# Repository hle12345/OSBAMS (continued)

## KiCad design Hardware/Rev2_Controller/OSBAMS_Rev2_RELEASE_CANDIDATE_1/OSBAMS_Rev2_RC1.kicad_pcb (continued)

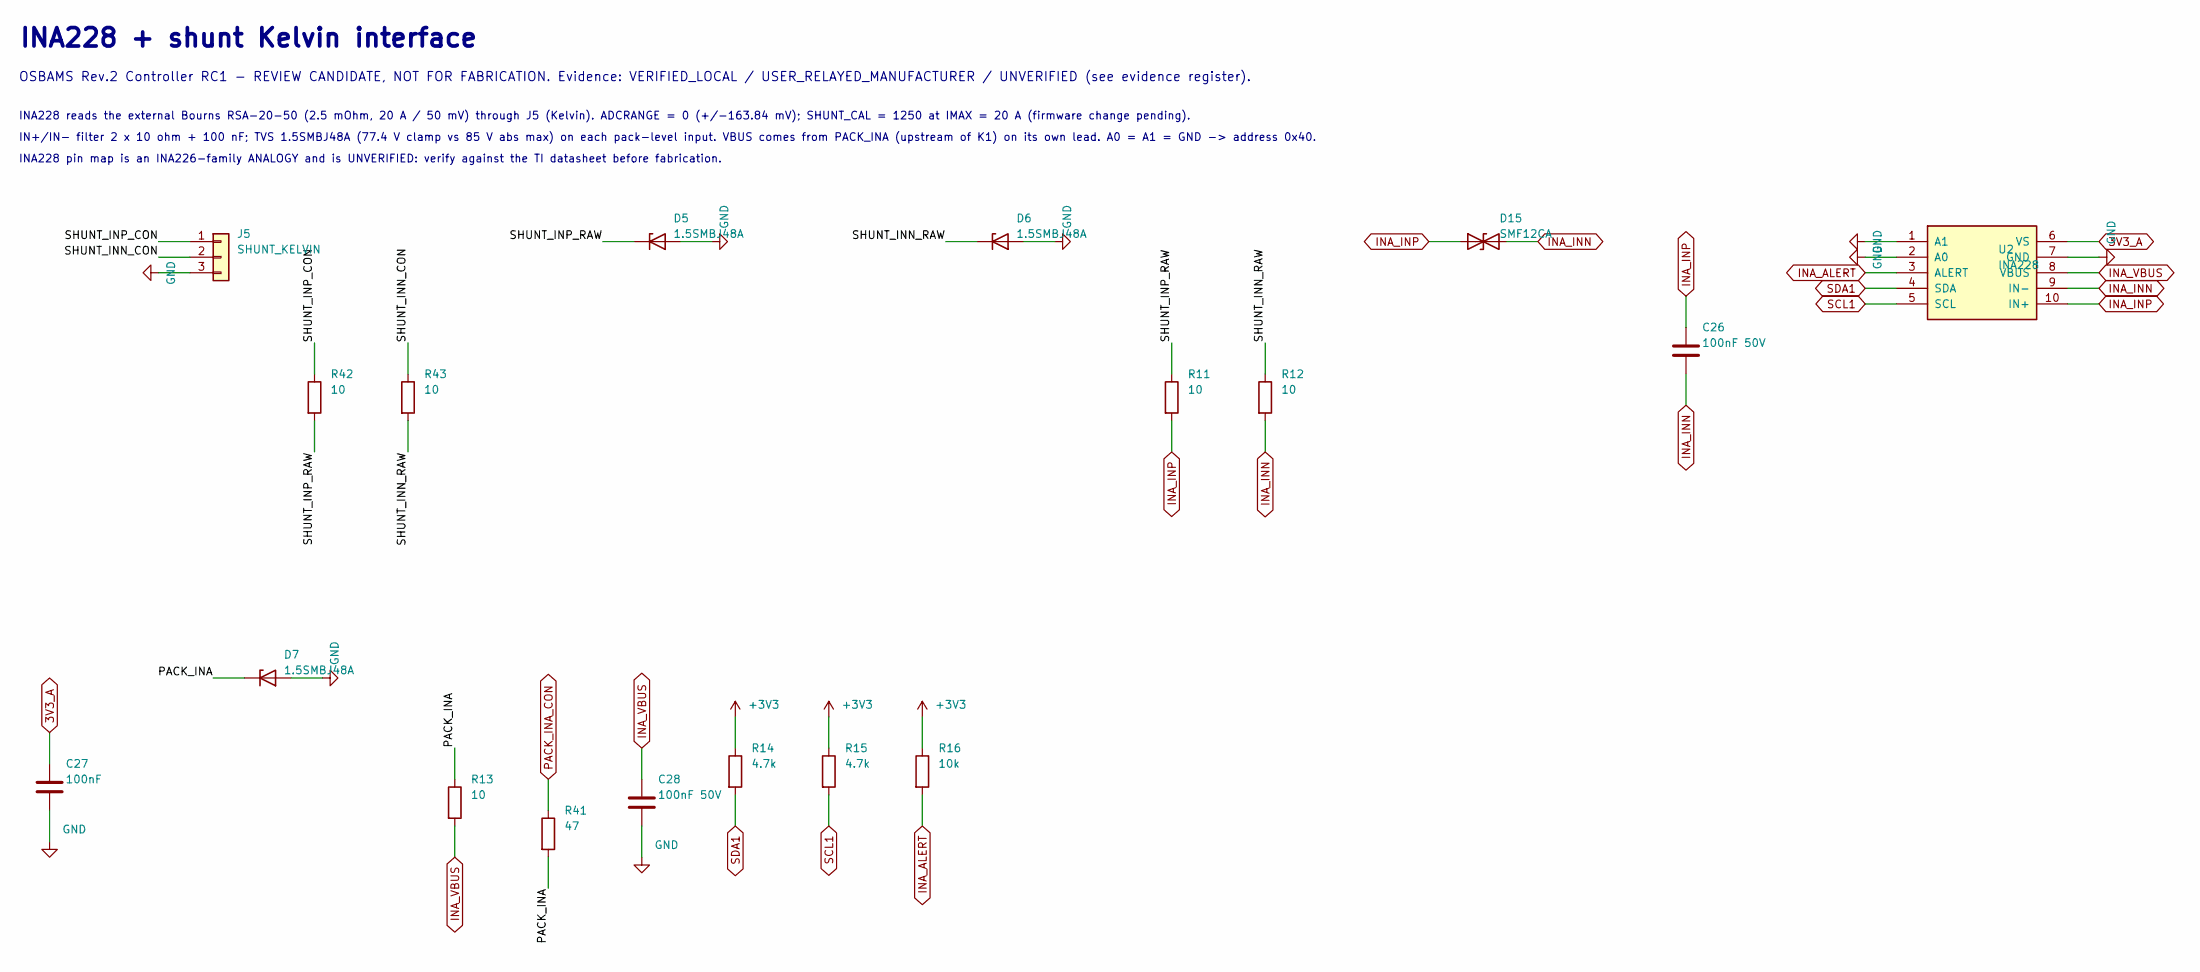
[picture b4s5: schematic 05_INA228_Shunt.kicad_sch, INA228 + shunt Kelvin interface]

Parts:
C26, C28: 100nF 50V; C_0603_1608Metric; MPN GRM188R71H104KA93D
C27: 100nF; C_0603_1608Metric; MPN GRM188R71H104KA93D
D5, D6, D7: 1.5SMBJ48A; D_SMB; MPN 1.5SMBJ48A
D15: SMF12CA; D_SMF; MPN SMF12CA
J5: SHUNT_KELVIN; Molex_KK-254_AE-6410-03A_1x03_P2.54mm_Vertical; MPN 22-27-2031
R11, R12, R13: 10; R_0603_1608Metric; MPN CRCW060310R0FKEA
R14, R15: 4.7k; R_0603_1608Metric; MPN CRCW06034K70FKEA
R16: 10k; R_0603_1608Metric; MPN CRCW060310K0FKEA
R41: 47; R_1206_3216Metric; MPN ERJ-P08F47R0V
R42, R43: 10; R_1206_3216Metric; MPN ERJ-P08F10R0V
U2: INA228; MSOP-10_3x3mm_P0.5mm; MPN INA228AIDGSR

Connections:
3V3_A: C27.1, U2.6 (VS); also elsewhere on the board
+3V3: R14.1, R15.1, R16.1; also elsewhere on the board
/05_INA228_Shunt/PACK_INA: D7.1 (K), R13.1, R41.2
/05_INA228_Shunt/SHUNT_INN_CON: J5.2, R43.1
/05_INA228_Shunt/SHUNT_INN_RAW: D6.1 (K), R12.1, R43.2
/05_INA228_Shunt/SHUNT_INP_CON: J5.1, R42.1
/05_INA228_Shunt/SHUNT_INP_RAW: D5.1 (K), R11.1, R42.2
GND: C27.2, C28.2, D5.2 (A), D6.2 (A), D7.2 (A), J5.3, U2.1 (A1), U2.2 (A0), U2.7 (GND); also elsewhere on the board
INA_ALERT: R16.2, U2.3 (ALERT); also elsewhere on the board
INA_INN: C26.2, D15.2 (A2), R12.2, U2.9 (IN-); also elsewhere on the board
INA_INP: C26.1, D15.1 (A1), R11.2, U2.10 (IN+); also elsewhere on the board
INA_VBUS: C28.1, R13.2, U2.8 (VBUS); also elsewhere on the board
PACK_INA_CON: R41.1; also elsewhere on the board
SCL1: R15.2, U2.5 (SCL); also elsewhere on the board
SDA1: R14.2, U2.4 (SDA); also elsewhere on the board

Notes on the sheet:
INA228 pin map is an INA226-family ANALOGY and is UNVERIFIED: verify against the TI datasheet before fabrication.
IN+/IN- filter 2 x 10 ohm + 100 nF; TVS 1.5SMBJ48A (77.4 V clamp vs 85 V abs max) on each pack-level input. VBUS comes from PACK_INA (upstream of K1) on its own lead. A0 = A1 = GND -> address 0x40.
OSBAMS Rev.2 Controller RC1 - REVIEW CANDIDATE, NOT FOR FABRICATION. Evidence: VERIFIED_LOCAL / USER_RELAYED_MANUFACTURER / UNVERIFIED (see evidence register).
INA228 + shunt Kelvin interface
INA228 reads the external Bourns RSA-20-50 (2.5 mOhm, 20 A / 50 mV) through J5 (Kelvin). ADCRANGE = 0 (+/-163.84 mV); SHUNT_CAL = 1250 at IMAX = 20 A (firmware change pending).

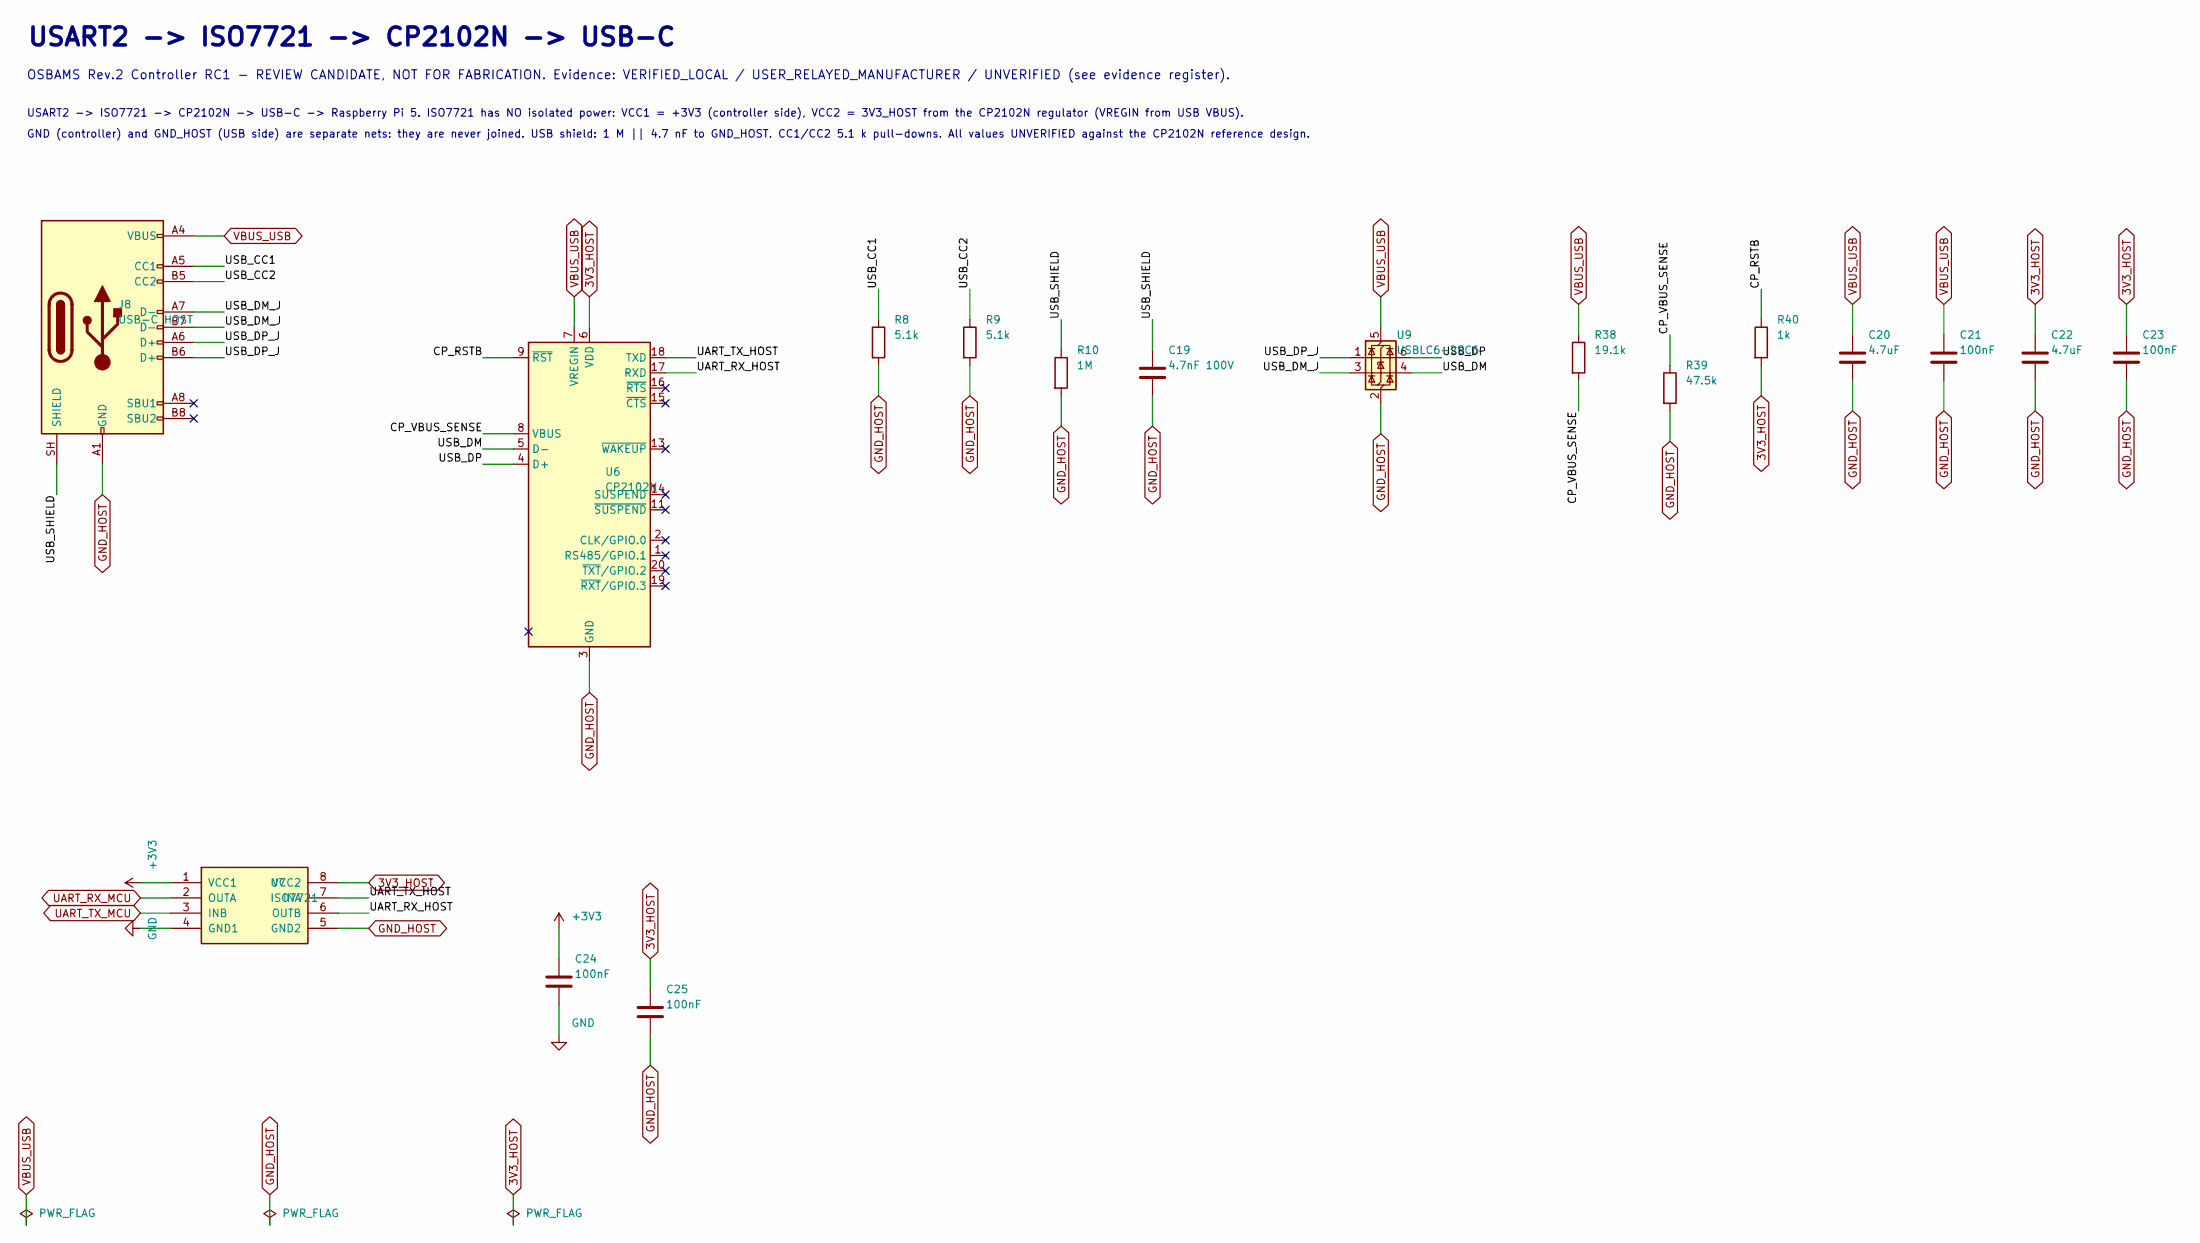
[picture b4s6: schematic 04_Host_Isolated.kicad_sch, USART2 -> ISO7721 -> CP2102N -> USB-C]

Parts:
C19: 4.7nF 100V; C_0805_2012Metric; MPN GRM21BR72A472KA01L
C20, C22: 4.7uF; C_0805_2012Metric; MPN GRM21BR61A475KA73L
C21, C23, C24, C25: 100nF; C_0603_1608Metric; MPN GRM188R71H104KA93D
J8: USB-C HOST; USB_C_Receptacle_GCT_USB4105-xx-A_16P_TopMnt_Horizontal; MPN USB4105-GF-A
R8, R9: 5.1k; R_0603_1608Metric; MPN CRCW06035K10FKEA
R10: 1M; R_0603_1608Metric; MPN CRCW06031M00FKEA
R38: 19.1k; R_0603_1608Metric; MPN CRCW060319K1FKEA
R39: 47.5k; R_0603_1608Metric; MPN CRCW060347K5FKEA
R40: 1k; R_0603_1608Metric; MPN CRCW06031K00FKEA
U6: CP2102N; SiliconLabs_QFN-20-1EP_3x3mm_P0.5mm_EP1.8x1.8mm; MPN CP2102N-A02-GQFN20
U7: ISO7721; SOIC-8_3.9x4.9mm_P1.27mm; MPN ISO7721DR
U9: USBLC6-2SC6; SOT-23-6; MPN USBLC6-2SC6

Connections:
3V3_HOST: C22.1, C23.1, C25.1, R40.2, U6.6 (VDD), U7.8 (VCC2); also elsewhere on the board
+3V3: C24.1, U7.1 (VCC1); also elsewhere on the board
/04_Host_Isolated/CP_RSTB: R40.1, U6.9 (~RST)
/04_Host_Isolated/CP_VBUS_SENSE: R38.2, R39.1, U6.8 (VBUS)
/04_Host_Isolated/UART_RX_HOST: U6.17 (RXD), U7.6 (OUTB)
/04_Host_Isolated/UART_TX_HOST: U6.18 (TXD), U7.7 (INA)
/04_Host_Isolated/USB_CC1: J8.A5 (CC1), R8.1
/04_Host_Isolated/USB_CC2: J8.B5 (CC2), R9.1
/04_Host_Isolated/USB_DM: U6.5 (D-), U9.4 (I/O2)
/04_Host_Isolated/USB_DM_J: J8.A7 (D-), J8.B7 (D-), U9.3 (I/O2)
/04_Host_Isolated/USB_DP: U6.4 (D+), U9.6 (I/O1)
/04_Host_Isolated/USB_DP_J: J8.A6 (D+), J8.B6 (D+), U9.1 (I/O1)
/04_Host_Isolated/USB_SHIELD: C19.1, J8.SH (SHIELD), R10.1
GND: C24.2, U7.4 (GND1); also elsewhere on the board
GND_HOST: C19.2, C20.2, C21.2, C22.2, C23.2, C25.2, J8.A1 (GND), J8.A12 (GND), J8.B1 (GND), J8.B12 (GND), R8.2, R9.2, R10.2, R39.2, U6.3 (GND), U6.12 (GND), U6.21 (GND), U7.5 (GND2), U9.2 (GND); also elsewhere on the board
UART_RX_MCU: U7.2 (OUTA); also elsewhere on the board
UART_TX_MCU: U7.3 (INB); also elsewhere on the board
VBUS_USB: C20.1, C21.1, J8.A4 (VBUS), J8.A9 (VBUS), J8.B4 (VBUS), J8.B9 (VBUS), R38.1, U6.7 (VREGIN), U9.5 (VBUS)

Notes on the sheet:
GND (controller) and GND_HOST (USB side) are separate nets: they are never joined. USB shield: 1 M || 4.7 nF to GND_HOST. CC1/CC2 5.1 k pull-downs. All values UNVERIFIED against the CP2102N reference design.
USART2 -> ISO7721 -> CP2102N -> USB-C -> Raspberry Pi 5. ISO7721 has NO isolated power: VCC1 = +3V3 (controller side), VCC2 = 3V3_HOST from the CP2102N regulator (VREGIN from USB VBUS).
OSBAMS Rev.2 Controller RC1 - REVIEW CANDIDATE, NOT FOR FABRICATION. Evidence: VERIFIED_LOCAL / USER_RELAYED_MANUFACTURER / UNVERIFIED (see evidence register).
USART2 -> ISO7721 -> CP2102N -> USB-C

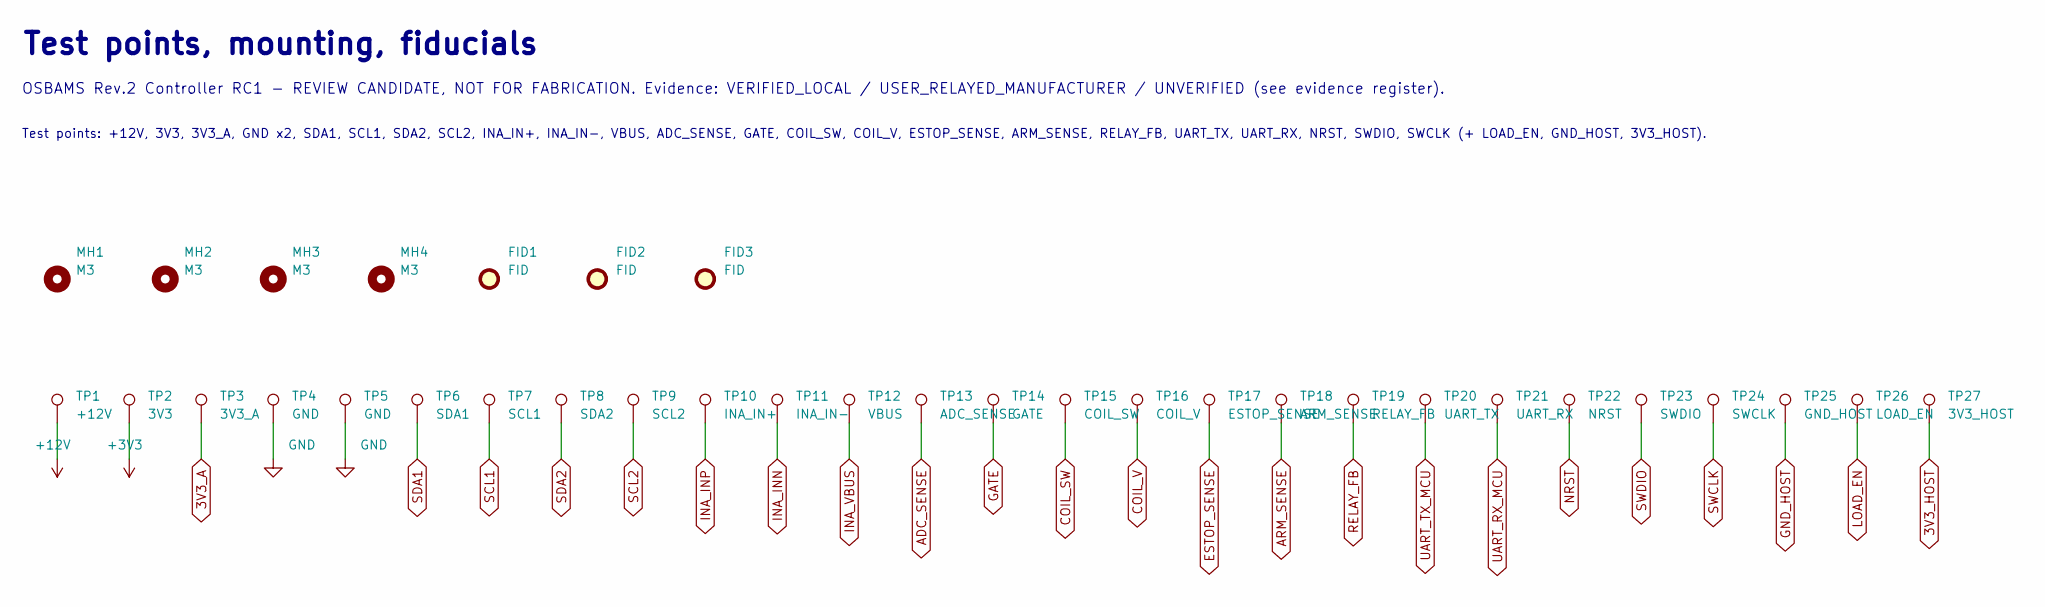
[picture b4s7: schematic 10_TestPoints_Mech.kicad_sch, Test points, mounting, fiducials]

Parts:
FID1, FID2, FID3: FID; Fiducial_1mm_Mask2mm; MPN (PCB feature)
MH1, MH2, MH3, MH4: M3; MountingHole_3.2mm_M3; MPN (PCB feature)
TP1: +12V; TestPoint_Pad_D1.5mm; MPN (PCB feature)
TP2: 3V3; TestPoint_Pad_D1.5mm; MPN (PCB feature)
TP3: 3V3_A; TestPoint_Pad_D1.5mm; MPN (PCB feature)
TP4, TP5: GND; TestPoint_Pad_D1.5mm; MPN (PCB feature)
TP6: SDA1; TestPoint_Pad_D1.5mm; MPN (PCB feature)
TP7: SCL1; TestPoint_Pad_D1.5mm; MPN (PCB feature)
TP8: SDA2; TestPoint_Pad_D1.5mm; MPN (PCB feature)
TP9: SCL2; TestPoint_Pad_D1.5mm; MPN (PCB feature)
TP10: INA_IN+; TestPoint_Pad_D1.5mm; MPN (PCB feature)
TP11: INA_IN-; TestPoint_Pad_D1.5mm; MPN (PCB feature)
TP12: VBUS; TestPoint_Pad_D1.5mm; MPN (PCB feature)
TP13: ADC_SENSE; TestPoint_Pad_D1.5mm; MPN (PCB feature)
TP14: GATE; TestPoint_Pad_D1.5mm; MPN (PCB feature)
TP15: COIL_SW; TestPoint_Pad_D1.5mm; MPN (PCB feature)
TP16: COIL_V; TestPoint_Pad_D1.5mm; MPN (PCB feature)
TP17: ESTOP_SENSE; TestPoint_Pad_D1.5mm; MPN (PCB feature)
TP18: ARM_SENSE; TestPoint_Pad_D1.5mm; MPN (PCB feature)
TP19: RELAY_FB; TestPoint_Pad_D1.5mm; MPN (PCB feature)
TP20: UART_TX; TestPoint_Pad_D1.5mm; MPN (PCB feature)
TP21: UART_RX; TestPoint_Pad_D1.5mm; MPN (PCB feature)
TP22: NRST; TestPoint_Pad_D1.5mm; MPN (PCB feature)
TP23: SWDIO; TestPoint_Pad_D1.5mm; MPN (PCB feature)
TP24: SWCLK; TestPoint_Pad_D1.5mm; MPN (PCB feature)
TP25: GND_HOST; TestPoint_Pad_D1.5mm; MPN (PCB feature)
TP26: LOAD_EN; TestPoint_Pad_D1.5mm; MPN (PCB feature)
TP27: 3V3_HOST; TestPoint_Pad_D1.5mm; MPN (PCB feature)

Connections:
3V3_A: TP3.1; also elsewhere on the board
3V3_HOST: TP27.1; also elsewhere on the board
+3V3: TP2.1; also elsewhere on the board
+12V: TP1.1; also elsewhere on the board
ADC_SENSE: TP13.1; also elsewhere on the board
ARM_SENSE: TP18.1; also elsewhere on the board
COIL_SW: TP15.1; also elsewhere on the board
COIL_V: TP16.1; also elsewhere on the board
ESTOP_SENSE: TP17.1; also elsewhere on the board
GATE: TP14.1; also elsewhere on the board
GND: TP4.1, TP5.1; also elsewhere on the board
GND_HOST: TP25.1; also elsewhere on the board
INA_INN: TP11.1; also elsewhere on the board
INA_INP: TP10.1; also elsewhere on the board
INA_VBUS: TP12.1; also elsewhere on the board
LOAD_EN: TP26.1; also elsewhere on the board
NRST: TP22.1; also elsewhere on the board
RELAY_FB: TP19.1; also elsewhere on the board
SCL1: TP7.1; also elsewhere on the board
SCL2: TP9.1; also elsewhere on the board
SDA1: TP6.1; also elsewhere on the board
SDA2: TP8.1; also elsewhere on the board
SWCLK: TP24.1; also elsewhere on the board
SWDIO: TP23.1; also elsewhere on the board
UART_RX_MCU: TP21.1; also elsewhere on the board
UART_TX_MCU: TP20.1; also elsewhere on the board

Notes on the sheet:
OSBAMS Rev.2 Controller RC1 - REVIEW CANDIDATE, NOT FOR FABRICATION. Evidence: VERIFIED_LOCAL / USER_RELAYED_MANUFACTURER / UNVERIFIED (see evidence register).
Test points: +12V, 3V3, 3V3_A, GND x2, SDA1, SCL1, SDA2, SCL2, INA_IN+, INA_IN-, VBUS, ADC_SENSE, GATE, COIL_SW, COIL_V, ESTOP_SENSE, ARM_SENSE, RELAY_FB, UART_TX, UART_RX, NRST, SWDIO, SWCLK (+ LOAD_EN, GND_HOST, 3V3_HOST).
Test points, mounting, fiducials

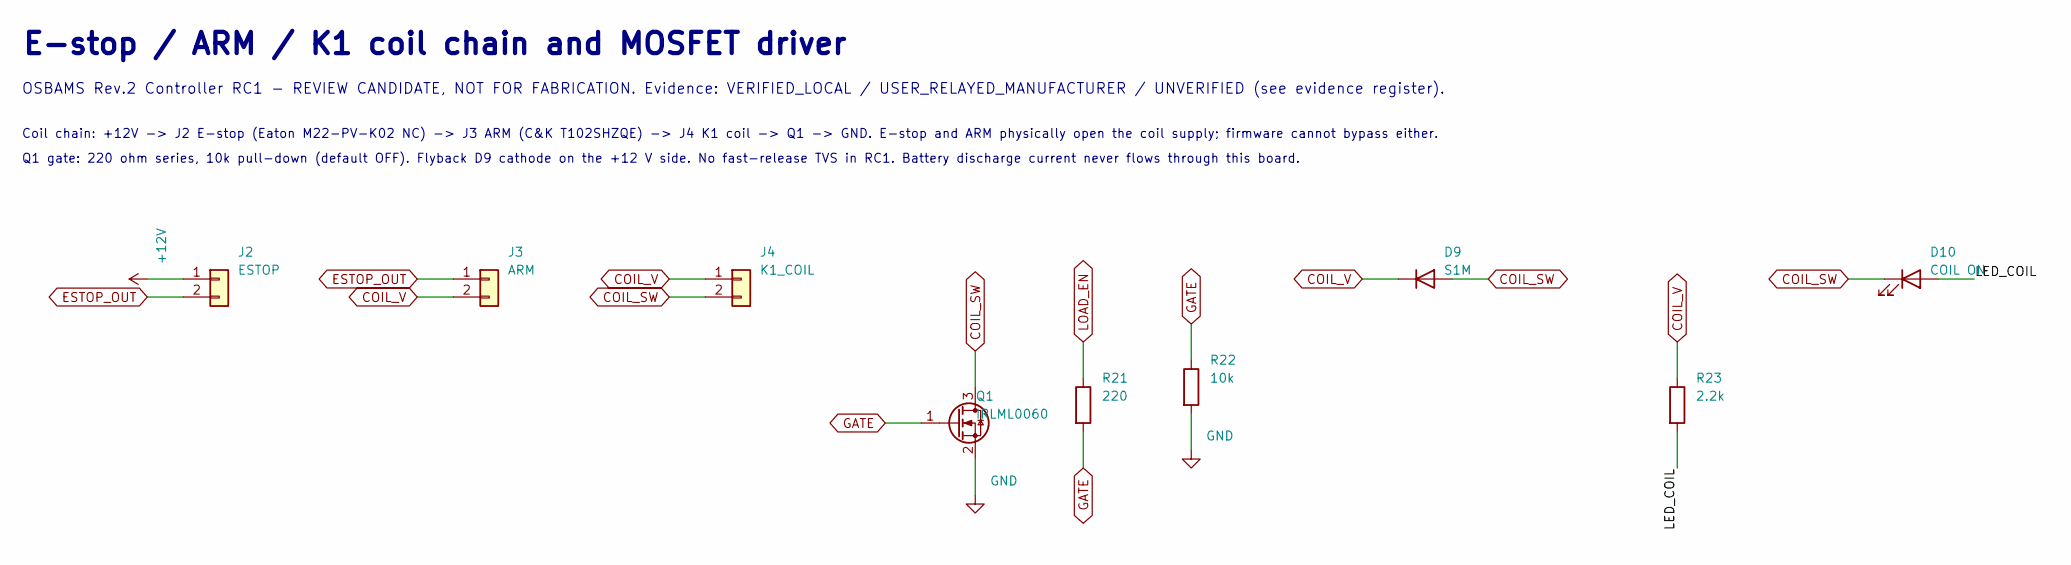
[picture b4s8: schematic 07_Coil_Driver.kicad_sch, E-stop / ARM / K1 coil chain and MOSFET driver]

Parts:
D9: S1M; D_SMA; MPN S1M-13-F
D10: COIL ON; LED_0805_2012Metric; MPN 150080AS75000
J2: ESTOP; EB21A-02-C; MPN EB21A-02-C
J3: ARM; EB21A-02-C; MPN EB21A-02-C
J4: K1_COIL; EB21A-02-C; MPN EB21A-02-C
Q1: IRLML0060; SOT-23; MPN IRLML0060TRPBF
R21: 220; R_0603_1608Metric; MPN CRCW0603220RFKEA
R22: 10k; R_0603_1608Metric; MPN CRCW060310K0FKEA
R23: 2.2k; R_0603_1608Metric; MPN CRCW06032K20FKEA

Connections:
+12V: J2.1; also elsewhere on the board
/07_Coil_Driver/LED_COIL: D10.2 (A), R23.2
COIL_SW: D9.2 (A), D10.1 (K), J4.2, Q1.3 (D); also elsewhere on the board
COIL_V: D9.1 (K), J3.2, J4.1, R23.1; also elsewhere on the board
ESTOP_OUT: J2.2, J3.1; also elsewhere on the board
GATE: Q1.1 (G), R21.2, R22.1; also elsewhere on the board
GND: Q1.2 (S), R22.2; also elsewhere on the board
LOAD_EN: R21.1; also elsewhere on the board

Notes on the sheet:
E-stop / ARM / K1 coil chain and MOSFET driver
Coil chain: +12V -> J2 E-stop (Eaton M22-PV-K02 NC) -> J3 ARM (C&K T102SHZQE) -> J4 K1 coil -> Q1 -> GND. E-stop and ARM physically open the coil supply; firmware cannot bypass either.
OSBAMS Rev.2 Controller RC1 - REVIEW CANDIDATE, NOT FOR FABRICATION. Evidence: VERIFIED_LOCAL / USER_RELAYED_MANUFACTURER / UNVERIFIED (see evidence register).
Q1 gate: 220 ohm series, 10k pull-down (default OFF). Flyback D9 cathode on the +12 V side. No fast-release TVS in RC1. Battery discharge current never flows through this board.

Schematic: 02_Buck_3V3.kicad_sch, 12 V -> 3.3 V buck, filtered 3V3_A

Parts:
C2: 10uF 50V; C_1210_3225Metric; MPN GRM32ER71H106KA12L
C3, C8: 100nF; C_0603_1608Metric; MPN GRM188R71H104KA93D
C4: 100nF (bootstrap); C_0603_1608Metric; MPN GRM188R71H104KA93D
C5, C6: 22uF; C_0805_2012Metric; MPN GRM21BR61A226ME44L
C7: 4.7uF; C_0805_2012Metric; MPN GRM21BR61A475KA73L
D3: 3V3 ON; LED_0805_2012Metric; MPN 150080GS75000
FB1: 600R@100MHz; L_0603_1608Metric; MPN BLM18PG601SN1D
L1: 10uH; L_Bourns_SRN6045TA; MPN SRN6045TA-100M
R1: 33.2k; R_0603_1608Metric; MPN CRCW060333K2FKEA
R2: 10k; R_0603_1608Metric; MPN CRCW060310K0FKEA
R3: 100k; R_0603_1608Metric; MPN CRCW0603100KFKEA
R4: 3.3k; R_0603_1608Metric; MPN CRCW06033K30FKEA
R5: 1k; R_0603_1608Metric; MPN CRCW06031K00FKEA
U3: LMR14006Y; SOT-23-6; MPN LMR14006YDDCR

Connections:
3V3_A: C7.1, C8.1, FB1.2, R4.1; also elsewhere on the board
+3V3: C5.1, C6.1, FB1.1, L1.2, R1.1, R5.1; also elsewhere on the board
+12V: C2.1, C3.1, R3.1, U3.5 (VIN); also elsewhere on the board
/02_Buck_3V3/BUCK_CB: C4.1, U3.1 (CB)
/02_Buck_3V3/BUCK_EN: R3.2, U3.4 (EN)
/02_Buck_3V3/BUCK_FB: R1.2, R2.1, U3.3 (FB)
/02_Buck_3V3/BUCK_SW: C4.2, L1.1, U3.6 (SW)
/02_Buck_3V3/LED_3V3: D3.2 (A), R5.2
GND: C2.2, C3.2, C5.2, C6.2, C7.2, C8.2, D3.1 (K), R2.2, R4.2, U3.2 (GND); also elsewhere on the board

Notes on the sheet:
LMR14006Y (4-40 V, 600 mA, 2.1 MHz, VREF 0.765 V: user-relayed). Vout = 0.765 x (1 + R1/R2) = 0.765 x (1 + 33.2k/10k) = 3.305 V.
12 V -> 3.3 V buck, filtered 3V3_A
OSBAMS Rev.2 Controller RC1 - REVIEW CANDIDATE, NOT FOR FABRICATION. Evidence: VERIFIED_LOCAL / USER_RELAYED_MANUFACTURER / UNVERIFIED (see evidence register).
R4 3.3k: permanent bleeder on 3V3_A; limits the rail to < 1 V if PACK+ back-feeds the MCU pin while the board is unpowered (calculations section 1.1).
Hot loop: C2/C3 - U3 VIN/GND - SW - L1 kept tiny in layout. No 5 V rail. 3V3_A = 3V3 through ferrite FB1 + 4.7 uF + 100 nF (VDDA, INA228).

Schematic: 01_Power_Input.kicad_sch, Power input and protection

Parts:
C1: 10uF 50V; C_1210_3225Metric; MPN GRM32ER71H106KA12L
D1: SMBJ15A; D_SMB; MPN SMBJ15A
D2: SS14; D_SMA; MPN SS14-E3/61T
F1: 1A fast; Fuse_1206_3216Metric; MPN 0453001.MR
J1: 12V_IN; EB21A-02-C; MPN EB21A-02-C

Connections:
+12V: C1.1, D1.1 (K), D2.1 (K); also elsewhere on the board
/01_Power_Input/12V_F: D2.2 (A), F1.2
/01_Power_Input/12V_RAW: F1.1, J1.1
GND: C1.2, D1.2 (A), J1.2; also elsewhere on the board

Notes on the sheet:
Diode polarity: Device:D / D_Schottky / D_Zener pin 1 = cathode (K); KiCad SMA/SMB footprints pad 1 = cathode - verified by tools in checks.py (netlist polarity check).
OSBAMS Rev.2 Controller RC1 - REVIEW CANDIDATE, NOT FOR FABRICATION. Evidence: VERIFIED_LOCAL / USER_RELAYED_MANUFACTURER / UNVERIFIED (see evidence register).
Power input and protection
J1: 12 V control input (XDR-75-12 set and verified at 12.0 V). F1 1 A fast, D2 Schottky reverse-polarity block (0.4 V drop), TVS D1 SMBJ15A across +12V AFTER D2 (reverse polarity is blocked, not clamped).

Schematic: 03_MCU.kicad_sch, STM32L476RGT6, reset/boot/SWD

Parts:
C10, C11, C12, C13, C14, C17, C18: 100nF; C_0603_1608Metric; MPN GRM188R71H104KA93D
C15: 4.7uF; C_0805_2012Metric; MPN GRM21BR61A475KA73L
C16: 1uF; C_0805_2012Metric; MPN GRM21BR71C105KA01L
D4: HEARTBEAT; LED_0805_2012Metric; MPN 150080GS75000
J9: SWD; PinHeader_2x05_P1.27mm_Vertical_SMD; MPN FTSH-105-01-L-DV-K
JP1: BOOT0; PinHeader_1x02_P2.54mm_Vertical; MPN TSW-102-07-G-S
R6: 10k; R_0603_1608Metric; MPN CRCW060310K0FKEA
R7: 1k; R_0603_1608Metric; MPN CRCW06031K00FKEA
SW1: RESET; SW_SPST_PTS810; MPN PTS810SJM250SMTRLFS
U1: STM32L476RGT6; LQFP-64_10x10mm_P0.5mm; MPN STM32L476RGT6

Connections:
3V3_A: C16.1, C17.1, U1.13 (VDDA); also elsewhere on the board
+3V3: C10.1, C11.1, C12.1, C13.1, C14.1, C15.1, J9.1 (VTref), JP1.1, U1.1 (VBAT), U1.19 (VDD), U1.32 (VDD), U1.48 (VDDUSB), U1.64 (VDD); also elsewhere on the board
/03_MCU/BOOT0: JP1.2, R6.1, U1.60 (BOOT0)
/03_MCU/LED_HB: D4.2 (A), R7.2
/03_MCU/LED_HB_PIN: R7.1, U1.21 (PA5)
/03_MCU/SWO: J9.6 (SWO/TDO), U1.55 (PB3)
ADC_SENSE: U1.15 (PA1); also elsewhere on the board
ARM_SENSE: U1.51 (PC10); also elsewhere on the board
ESTOP_SENSE: U1.14 (PA0); also elsewhere on the board
GND: C10.2, C11.2, C12.2, C13.2, C14.2, C15.2, C16.2, C17.2, C18.2, D4.1 (K), J9.3 (GND), J9.5 (GND), J9.9 (GNDDetect), R6.2, SW1.2, U1.12 (VSSA), U1.18 (VSS), U1.31 (VSS), U1.47 (VSS), U1.63 (VSS); also elsewhere on the board
INA_ALERT: U1.26 (PB0); also elsewhere on the board
LOAD_EN: U1.39 (PC8); also elsewhere on the board
NRST: C18.1, J9.10 (~RESET), SW1.1, U1.7 (NRST); also elsewhere on the board
RELAY_FB: U1.40 (PC9); also elsewhere on the board
SCL1: U1.61 (PB8); also elsewhere on the board
SCL2: U1.29 (PB10); also elsewhere on the board
SDA1: U1.62 (PB9); also elsewhere on the board
SDA2: U1.30 (PB11); also elsewhere on the board
SWCLK: J9.4 (SWCLK/TCK), U1.49 (PA14); also elsewhere on the board
SWDIO: J9.2 (SWDIO/TMS), U1.46 (PA13); also elsewhere on the board
UART_RX_MCU: U1.17 (PA3); also elsewhere on the board
UART_TX_MCU: U1.16 (PA2); also elsewhere on the board

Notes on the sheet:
STM32L476RGT6, reset/boot/SWD
Unused pins carry no-connect flags and are configured analog/pulled low in firmware. BOOT0: 10k pull-down + jumper JP1 to 3V3 (ROM bootloader).
PA1 ADC_SENSE (VREFINT-corrected), PA2/PA3 USART2, PB8/PB9 I2C1 (INA228), PB10/PB11 I2C2 (TC74, <= 100 kHz), PB0 INA228 ALERT, PC8 LOAD_EN (default low), PA5 heartbeat, SWD on J9.
STM32L476RGT6 direct. HSI16 -> PLL 80 MHz (no crystal), no LSE, USB unused. PA0 ESTOP_SENSE (LOW = healthy), PC9 RELAY_FB (active low), PC10 ARM_SENSE (HIGH = armed, status only).
OSBAMS Rev.2 Controller RC1 - REVIEW CANDIDATE, NOT FOR FABRICATION. Evidence: VERIFIED_LOCAL / USER_RELAYED_MANUFACTURER / UNVERIFIED (see evidence register).

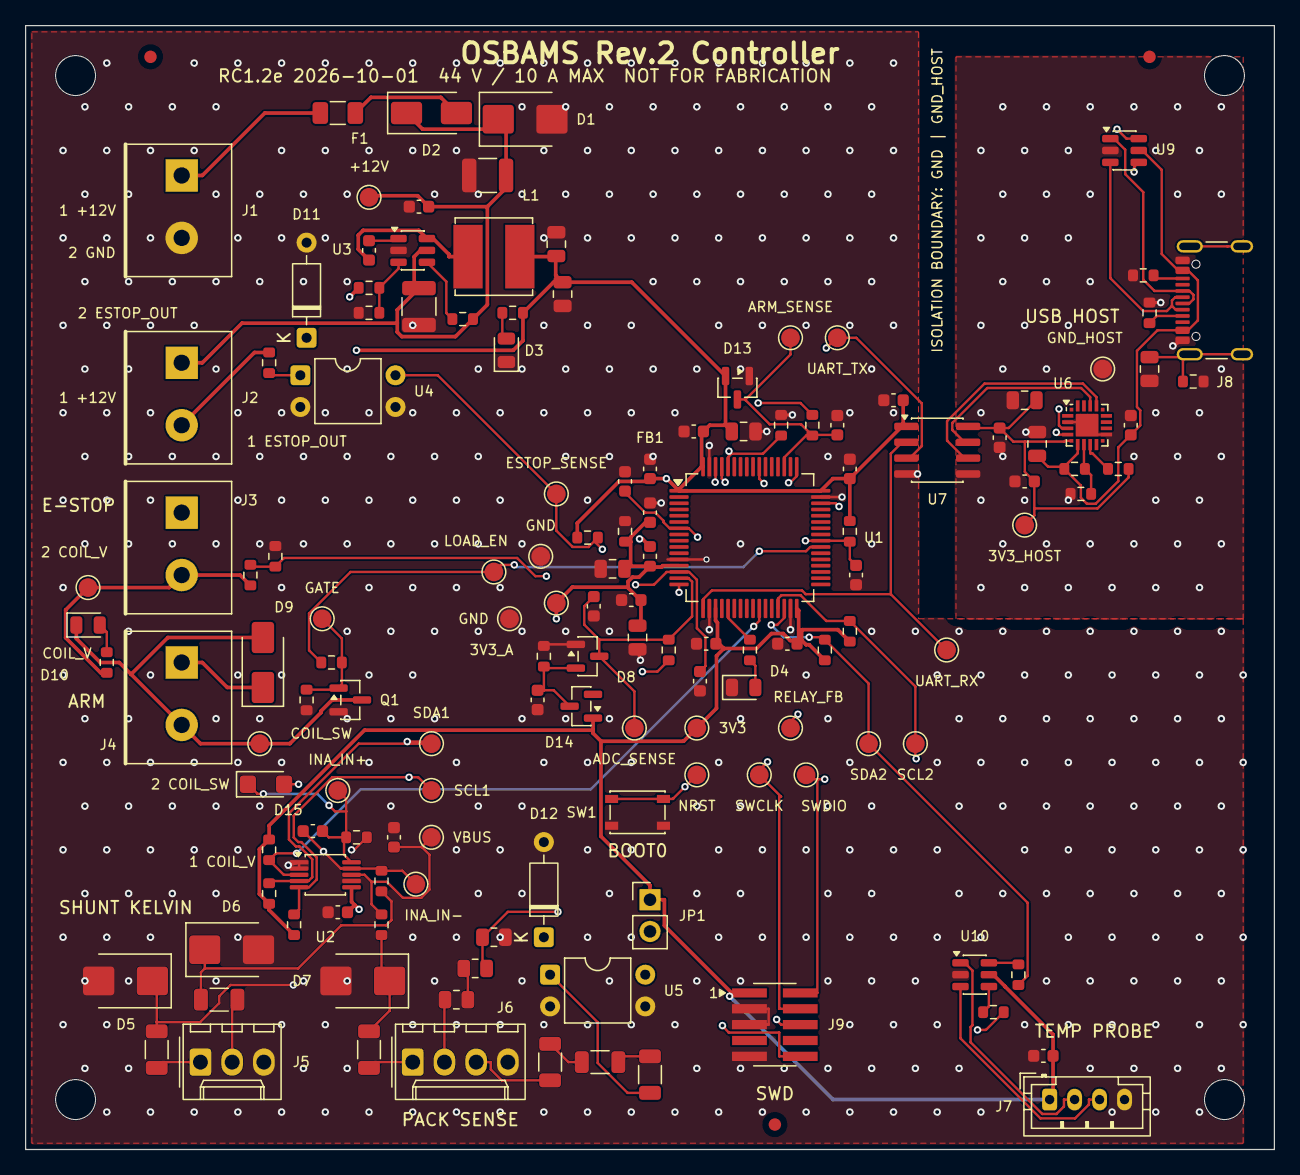
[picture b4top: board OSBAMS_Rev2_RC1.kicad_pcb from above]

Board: 4 copper layers, 100.0 x 90.0 mm, 149 parts (0 on the bottom side), 72 nets.

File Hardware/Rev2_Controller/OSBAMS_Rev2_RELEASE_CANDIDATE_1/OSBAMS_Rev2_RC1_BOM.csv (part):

Item,Reference(s),Qty / board,Qty for 5 boards,Value,Description,Manufacturer,MPN,MPN suffix status,Package,Footprint,Evidence Status,Lifecycle,Primary Supplier,Supplier SKU,Stock Check Date,Approved Alternate,PCBWay Source / Consign,DNP,Notes
1,J1,1,5,12V_IN,"2-pos 5.00 mm right-angle screw terminal, 8 A / 300 V (footprint from Adam Tech drawing EB21A-XX-C rev B)",Adam Tech,EB21A-02-C,"confirmed (Adam Tech drawing EB21A-XX-C, read locally; owned part)",EB21A-02-C,OSBAMS_Rev2:EB21A-02-C,USER_RELAYED_MANUFACTURER,UNKNOWN (not checked),Mouser / Digi-Key (authorized) - NOT QUERIED,NOT CHECKED (distributor sites unreachable from the build environment),NOT CHECKED,"Phoenix MKDS 1/2-5,08 (different footprint) (UNVERIFIED alternate)",CONSIGN (owned: 5) or PCBWay source,no,"Pin 1 +12 V, pin 2 GND. XDR-75-12 set to 12.0 V"
2,F1,1,5,1A fast,1 A fast fuse 1206 32 V,Littelfuse,0453001.MR,orderable suffix NOT yet confirmed against a distributor/manufacturer listing,1206,Fuse:Fuse_1206_3216Metric,UNVERIFIED,UNKNOWN (not checked),Mouser / Digi-Key (authorized) - NOT QUERIED,NOT CHECKED (distributor sites unreachable from the build environment),NOT CHECKED,Littelfuse 0466001.NR (UNVERIFIED alternate),PCBWay source,no,
3,D2,1,5,SS14,1 A 40 V Schottky SMA (series reverse-polarity),Vishay,SS14-E3/61T,orderable suffix NOT yet confirmed against a distributor/manufacturer listing,SMA,Diode_SMD:D_SMA,UNVERIFIED,UNKNOWN (not checked),Mouser / Digi-Key (authorized) - NOT QUERIED,NOT CHECKED (distributor sites unreachable from the build environment),NOT CHECKED,Diodes Inc SS14-13-F (UNVERIFIED alternate),PCBWay source,no,
4,D1,1,5,SMBJ15A,Unidirectional TVS 15 V standoff 600 W (K = pin 1),Littelfuse,SMBJ15A,orderable suffix NOT yet confirmed against a distributor/manufacturer listing,SMB,Diode_SMD:D_SMB,USER_RELAYED_MANUFACTURER,UNKNOWN (not checked),Mouser / Digi-Key (authorized) - NOT QUERIED,NOT CHECKED (distributor sites unreachable from the build environment),NOT CHECKED,Bourns SMBJ15A-Q (UNVERIFIED alternate),CONSIGN or PCBWay source,no,
5,"C1, C2",2,10,10uF 50V,10 uF 50 V X7R 1210 (12 V rail / buck input),Murata,GRM32ER71H106KA12L,orderable suffix NOT yet confirmed against a distributor/manufacturer listing,1210,Capacitor_SMD:C_1210_3225Metric,UNVERIFIED,UNKNOWN (not checked),Mouser / Digi-Key (authorized) - NOT QUERIED,NOT CHECKED (distributor sites unreachable from the build environment),NOT CHECKED,TDK C3225X7R1H106K250AC (UNVERIFIED alternate),PCBWay source,no,
6,U3,1,5,LMR14006Y,LMR14006Y 4-40 V 0.6 A 2.1 MHz buck SOT-23-6 (PIN MAP UNVERIFIED),Texas Instruments,LMR14006YDDCR,orderable suffix NOT yet confirmed against a distributor/manufacturer listing,SOT-23-6,Package_TO_SOT_SMD:SOT-23-6,USER_RELAYED_MANUFACTURER,ACTIVE (user-confirmed),Mouser / Digi-Key (authorized) - NOT QUERIED,NOT CHECKED (distributor sites unreachable from the build environment),NOT CHECKED,LMR14006XDDCR (700 kHz variant: inductor change) (UNVERIFIED alternate),PCBWay source,no,
7,"C3, C8, C10, C11, C12, C13, C14, C17, C18, C21, C23, C24, C25, C27, C29, C32, C33, C34",18,90,100nF,100 nF 50 V X7R 0603,Murata,GRM188R71H104KA93D,orderable suffix NOT yet confirmed against a distributor/manufacturer listing,0603,Capacitor_SMD:C_0603_1608Metric,UNVERIFIED,UNKNOWN (not checked),Mouser / Digi-Key (authorized) - NOT QUERIED,NOT CHECKED (distributor sites unreachable from the build environment),NOT CHECKED,Samsung CL10B104KB8NNNC (UNVERIFIED alternate),PCBWay source,no,At J7; INA228 VS; ISO7721 VCC1; ISO7721 VCC2; VBAT pin 1; VDD pin 19; VDD pin 32; VDD pin 64; VDDA; VDDUSB pin 48
8,C4,1,5,100nF (bootstrap),100 nF 50 V X7R 0603,Murata,GRM188R71H104KA93D,orderable suffix NOT yet confirmed against a distributor/manufacturer listing,0603,Capacitor_SMD:C_0603_1608Metric,UNVERIFIED,UNKNOWN (not checked),Mouser / Digi-Key (authorized) - NOT QUERIED,NOT CHECKED (distributor sites unreachable from the build environment),NOT CHECKED,Samsung CL10B104KB8NNNC (UNVERIFIED alternate),PCBWay source,no,
9,L1,1,5,10uH,"10 uH shielded inductor 6x6 mm (10 uH +/-20 %, DCR 52 mohm, Irms 3.2 A, Isat 4.6 A: Bourns datasheet read locally)",Bourns,SRN6045TA-100M,"confirmed (Bourns datasheet table, read locally)",L_Bourns_SRN6045TA,Inductor_SMD:L_Bourns_SRN6045TA,VERIFIED_LOCAL,UNKNOWN (not checked),Mouser / Digi-Key (authorized) - NOT QUERIED,NOT CHECKED (distributor sites unreachable from the build environment),NOT CHECKED,Wurth 744043100 (UNVERIFIED alternate),PCBWay source,no,
10,R1,1,5,33.2k,33.2k 1 % thick film 0603,Vishay Dale,CRCW060333K2FKEA,orderable suffix NOT yet confirmed against a distributor/manufacturer listing,0603,Resistor_SMD:R_0603_1608Metric,UNVERIFIED,UNKNOWN (not checked),Mouser / Digi-Key (authorized) - NOT QUERIED,NOT CHECKED (distributor sites unreachable from the build environment),NOT CHECKED,Yageo RC0603-FR-07 series (UNVERIFIED alternate),PCBWay source,no,
11,"R2, R6, R16, R22, R37",5,25,10k,10k 1 % thick film 0603,Vishay Dale,CRCW060310K0FKEA,orderable suffix NOT yet confirmed against a distributor/manufacturer listing,0603,Resistor_SMD:R_0603_1608Metric,UNVERIFIED,UNKNOWN (not checked),Mouser / Digi-Key (authorized) - NOT QUERIED,NOT CHECKED (distributor sites unreachable from the build environment),NOT CHECKED,Yageo RC0603-FR-07 series (UNVERIFIED alternate),PCBWay source,no,Bleeds the isolated clamp rail; Default OFF
12,"R3, R31",2,10,100k,100k 1 % thick film 0603,Vishay Dale,CRCW0603100KFKEA,orderable suffix NOT yet confirmed against a distributor/manufacturer listing,0603,Resistor_SMD:R_0603_1608Metric,UNVERIFIED,UNKNOWN (not checked),Mouser / Digi-Key (authorized) - NOT QUERIED,NOT CHECKED (distributor sites unreachable from the build environment),NOT CHECKED,Yageo RC0603-FR-07 series (UNVERIFIED alternate),PCBWay source,no,
13,"C5, C6",2,10,22uF,22 uF 10 V X5R 0805 (derates ~50 % at 3.3 V),Murata,GRM21BR61A226ME44L,orderable suffix NOT yet confirmed against a distributor/manufacturer listing,0805,Capacitor_SMD:C_0805_2012Metric,UNVERIFIED,UNKNOWN (not checked),Mouser / Digi-Key (authorized) - NOT QUERIED,NOT CHECKED (distributor sites unreachable from the build environment),NOT CHECKED,Samsung CL21A226MPQNNNE (UNVERIFIED alternate),PCBWay source,no,
14,FB1,1,5,600R@100MHz,Ferrite bead 600 ohm @ 100 MHz 0603,Murata,BLM18PG601SN1D,orderable suffix NOT yet confirmed against a distributor/manufacturer listing,0603,Inductor_SMD:L_0603_1608Metric,UNVERIFIED,UNKNOWN (not checked),Mouser / Digi-Key (authorized) - NOT QUERIED,NOT CHECKED (distributor sites unreachable from the build environment),NOT CHECKED,TDK MMZ1608B601CTAH0 (UNVERIFIED alternate),PCBWay source,no,
15,"C7, C15, C20, C22",4,20,4.7uF,4.7 uF 10 V X5R 0805,Murata,GRM21BR61A475KA73L,orderable suffix NOT yet confirmed against a distributor/manufacturer listing,0805,Capacitor_SMD:C_0805_2012Metric,UNVERIFIED,UNKNOWN (not checked),Mouser / Digi-Key (authorized) - NOT QUERIED,NOT CHECKED (distributor sites unreachable from the build environment),NOT CHECKED,Samsung CL21A475KPFNNNE (UNVERIFIED alternate),PCBWay source,no,"CP2102N VDD: 4.7 uF + 0.1 uF required per power pin (Silicon Labs datasheet, read locally)"
16,R4,1,5,3.3k,3.3k 1 % thick film 0603,Vishay Dale,CRCW06033K30FKEA,orderable suffix NOT yet confirmed against a distributor/manufacturer listing,0603,Resistor_SMD:R_0603_1608Metric,UNVERIFIED,UNKNOWN (not checked),Mouser / Digi-Key (authorized) - NOT QUERIED,NOT CHECKED (distributor sites unreachable from the build environment),NOT CHECKED,Yageo RC0603-FR-07 series (UNVERIFIED alternate),PCBWay source,no,Permanent bleeder: keeps 3V3A < 1 V if PACK+ back-feeds through PA1 with the board unpowered
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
